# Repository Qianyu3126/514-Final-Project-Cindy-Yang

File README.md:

# Anti-sedentary Reminder  
A product designed to prevent prolonged sitting, using a wearable waist sensor that interacts with a desktop object to visualize the health risks of sitting too long. Through lighting effects and the posture of a small figurine on the desktop piece, the product reminds users to stand up and move.  
  
## Sensor Device  
  
## Display Device  
  
## System Architecture

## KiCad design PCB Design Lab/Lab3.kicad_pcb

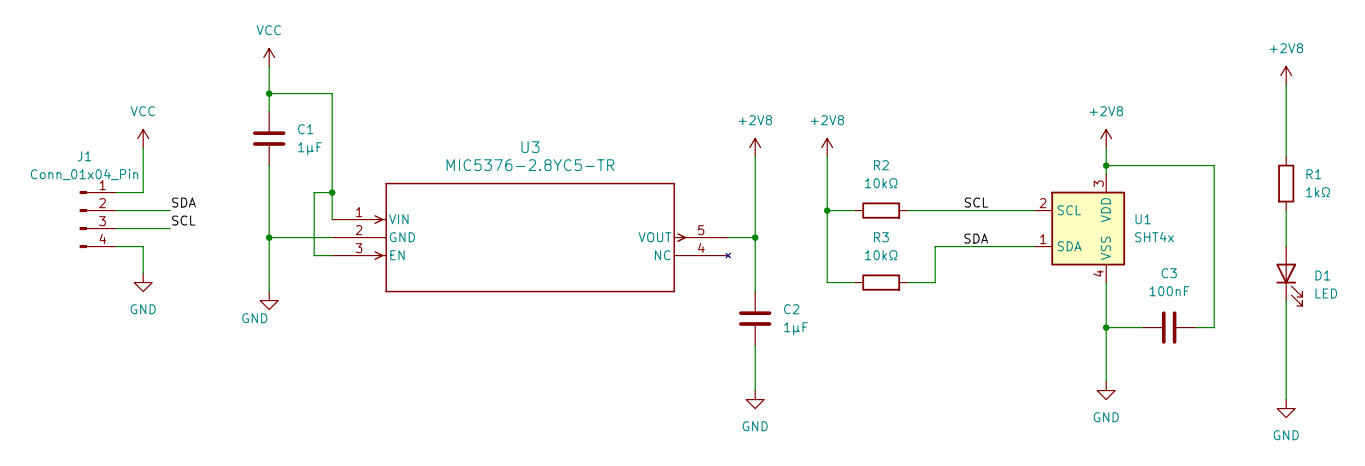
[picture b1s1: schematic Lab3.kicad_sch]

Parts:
C1, C2: 1μF; C_0603_1608Metric_Pad1.08x0.95mm_HandSolder
C3: 100nF; C_0603_1608Metric_Pad1.08x0.95mm_HandSolder
D1: LED; LED_0603_1608Metric_Pad1.05x0.95mm_HandSolder
J1: Conn_01x04_Pin; PinHeader_1x04_P2.54mm_Vertical
R1: 1kΩ; R_0603_1608Metric_Pad0.98x0.95mm_HandSolder
R2, R3: 10kΩ; R_0603_1608Metric_Pad0.98x0.95mm_HandSolder
U1: SHT4x; Sensirion_DFN-4_1.5x1.5mm_P0.8mm_SHT4x_NoCentralPad
U3: MIC5376-2.8YC5-TR; SC-70_C5_MCH

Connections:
+2V8: C2.1, C3.2, R1.1, R2.1, R3.1, U1.3 (VDD), U3.5 (VOUT)
/SCL: J1.3, R2.2, U1.2 (SCL)
/SDA: J1.2, R3.2, U1.1 (SDA)
GND: C1.2, C2.2, C3.1, D1.1 (K), J1.4, U1.4 (VSS), U3.2 (GND)
unnamed: D1.2 (A), R1.2
VCC: C1.1, J1.1, U3.1 (VIN), U3.3 (EN)

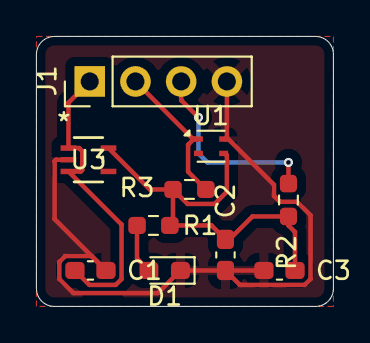
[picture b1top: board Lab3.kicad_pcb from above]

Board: 2 copper layers, 16.5 x 15.0 mm, 10 parts (0 on the bottom side), 6 nets.

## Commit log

2026-01-20 012026
2026-01-20 Update 012026
2026-01-21 Add boost converter datasheet
2026-01-27 012626
2026-01-27 kicad012626
2026-01-30 lab3 012926
2026-01-30 Add PCB Design Lab files
2026-01-30 012926
2026-02-05 Add Battery Management Lab folder
